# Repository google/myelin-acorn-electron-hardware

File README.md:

# MOVED to https://github.com/myelin/acorn-hardware

Any future development will happen over there.

myelin-acorn-electron-hardware
==============================

The [Acorn Electron](https://en.wikipedia.org/wiki/Acorn_Electron) is a British computer that was very popular in the UK and New
Zealand in the 80s, and was the first computer I ever used, in 1985.  I acquired
one on eBay in 2016, and started hacking on hardware expansions for it a little
later.  In the meantime I've also acquired a BBC Model B, and some BBC Master
128 motherboards.  This repository contains various hardware expansions I've
designed for the three machines.

Background: https://www.theregister.co.uk/2013/08/23/acorn_electron_history_at_30/

Designed by Phillip Pearson (philpearson@google.com)

This is not an official Google product.

Acorn Electron projects
-----------------------

- [standalone_cartridge_programmer](standalone_cartridge_programmer/):
  USB Acorn Electron cartridge interface, allowing read/write access
  to cartridges without an actual Electron / Plus 1.  (Built,
  verified.)

- [elk_pi_tube_direct](elk_pi_tube_direct/): Acorn Electron cartridge
  using a CPLD to provide address decoding and level shifting for a
  Raspberry Pi running PiTubeDirect.  (Built, verified.)

- [expansion_minispartan_breakout](expansion_minispartan_breakout/):
  Breakout board for the Electron's rear expansion connector, with
  buffers and footprint to attach a Scarab miniSpartan6+ LX25 board.
  (Built, verified.)

- [minus_one](minus_one/): Acorn Electron expansion that provides
  three Plus 1 workalike cartridge slots.  (Built, verified.)

- [32kb_flash_cartridge](32kb_flash_cartridge/): Simple Acorn Electron
  cartridge with two 16kB flash banks.  (Built, verified standard PCB.
  Mini PCB built but had a PCB error.)

Cross-platform projects
-----------------------

- [cpu_socket_expansion](cpu_socket_expansion/): Mezzanine board that attaches
  to the CPU socket of a BBC or Electron and translates between 5V TTL and 3.3V
  CMOS levels. (Built, tested.)

- [cpu_socket_minispartan_daughterboard](cpu_socket_minispartan_daughterboard/):
  Attaches to a cpu_socket_expansion board and connects a miniSpartan6+ FPGA
  board and a Raspberry Pi Zero running PiTubeDirect.  (Built, tested.)

- [spi_sd_card](spi_sd_card/): Experimental implementation of the interface
  used by MMFS to access SD cards, for the CPLD on an elk_pi_tube_direct board.
  (Code only.)

- [fx2_tube_cartridge_adapter](fx2_tube_cartridge_adapter/): Adapter to allow
  connecting an FX2-based logic analyzer board to the BBC Tube interface or
  as an Electron cartridge.  (Partly tested.)

- [bbc_power_distribution](bbc_power_distribution/): Small board to
  make it easy to power a Model B or Master motherboard from a 5V
  power supply with a barrel jack or Micro USB output.  Uses an
  LTC1983 to generate -5V, so you don't need to provide it externally.

BBC Model B projects
--------------------

- [new_bbc_bringup](new_bbc_bringup/): Notes on modernizing a BBC Model B,
  with flash and sideways RAM, and an emulated disk interface.

- [upurs_usb_port](upurs_usb_port/): Code to run on an ATMEGA32U4 to
  use it as a USB to serial adapter for UPURS.  (Flaky.)

- [serial_sd_adapter](serial_sd_adapter/): VHDL that runs on an
  elk_pi_tube_direct board and provides a fast serial port and SD card
  interface.  Also, a board that attaches to a BBC using the 1MHz Bus and
  provides the same interfaces.  (Built, tested serial port.  SD card interface
  untested.)

- [econet_from_scratch](econet_from_scratch/): USB Econet interface.
  (Untested.)

- [econet_hub](econet_hub/): Clock and bias circuit, with five Econet sockets,
  to connect a simple network together.  (Untested.)

BBC Master 128 projects
-----------------------

- [master_updateable_megarom](master_updateable_megarom/): BBC Master 128 MOS
  ROM replacement that can be reprogrammed while in the machine.  (Untested.)

- [emulated_keyboard](emulated_keyboard/): Code and VHDL to allow an attached
  computer to act as a keyboard for a BBC Master 128.  (Code only, verified.)

- [new_master_bringup](new_master_bringup/): Notes on getting a BBC Master 128
  motherboard to run without a keyboard or standard power supply.

Miscellaneous things that happened along the way
------------------------------------------------

- [atsamd11_pro_micro](atsamd11_pro_micro/): Tester board to experiment with
  USB on the Atmel ATSAMD11C14 chip.  (Untested.)

- [atsamd21_usb_host](atsamd21_usb_host/): Tester board to experiment with
  USB hosting on the Atmel ATSAMD21E18A chip.  (Untested.)

- [cherry_mx_keyswitch_tester](cherry_mx_keyswitch_tester/): Tester board to
  verify my Cherry MX keyswitch footprint before I order anything expensive.
  (Built, verified.)

Future project ideas
--------------------

- dual_ported_ram: Acorn Electron cartridge using a CPLD and a 128kB
  SRAM chip to implement dual ported RAM that can be read or written
  by both the Electron and a USB-attached computer.  (Working on the
  PCB layout.)

- expansion_debugger: Pro Micro, CPLD, and edge connector that can be
  connected to a Plus 1 or other Electron expansion for testing.
  (Just an idea so far.)

Installation notes
------------------

I use my own Python scripts for generating netlists, rather than entering
schematics through Kicad's eeschema package.  If you change the .py file in
any of the `pcb` folders, running 'make' (or 'make net') should rebuild the
netlist.

The Makefile will also plot gerbers once a .kicad_pcb file has been created.
This requires some messing around on macOS -- you have to copy the system
Python executable into the pcbnew folder.

Generating the previews linked from the `README.md` files requires pcb-tools,
which you can install using `python setup.py install` in the `third_party/pcb-tools` folder (after running `git submodule update --init`).  On macOS, first
install its dependencies with `brew install cairo pango`.

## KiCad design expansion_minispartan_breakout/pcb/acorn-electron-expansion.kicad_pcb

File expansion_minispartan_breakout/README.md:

expansion_minispartan_breakout
==============================

_Superseded by [cpu_socket_expansion](../cpu_socket_expansion/) and
[cpu_socket_minispartan_daughterboard](../cpu_socket_minispartan_daughterboard/)._

This board breaks out the expansion connector to 0.1" holes, and
provides the necessary level conversion and buffering to allow a
Scarab miniSpartan6+ board to interface with the Electron's expansion
connector.

I've assembled and tested one rev 1 board, with the miniSpartan6+ configured to
provide a few ROM banks, and it works pretty nicely.  I made some changes for
rev 2 to allow switching the direction of the address buffers, which would make
it possible to use a soft CPU in the FPGA (after removing the CPU from the
Electron's motherboard).  I never made a rev 2 board, however, as at that point
I [acquired a BBC Micro](../new_bbc_bringup/) and started working on more
portable hardware.

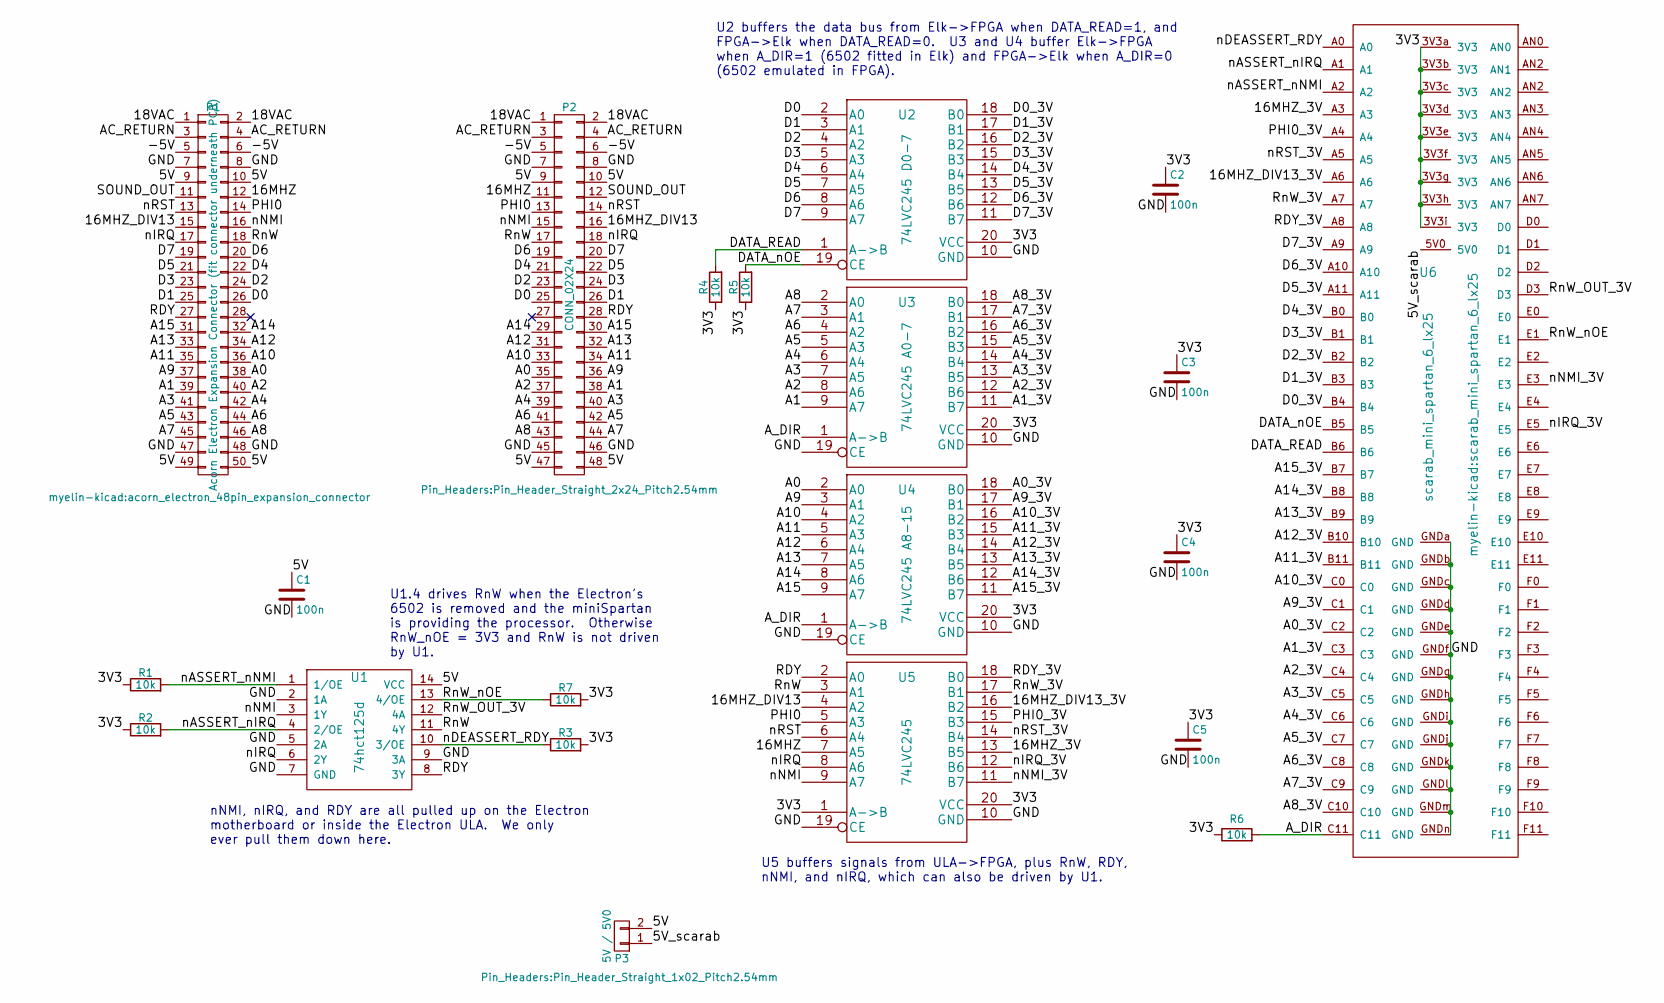
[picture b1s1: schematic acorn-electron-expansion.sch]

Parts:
C1, C2, C3, C4, C5: 100n; C0805_nosilkscreen
P1: Acorn Electron Expansion Connector (fit connector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; acorn_electron_48pin_expansion_connector
P2: CONN_02X24; Pin_Header_Straight_2x24_Pitch2.54mm
P3: 5V / 5V0; Pin_Header_Straight_1x02_Pitch2.54mm
R1, R2, R3, R4, R5: 10k; R0805_nosilkscreen
R6, R7: 10k; R_0805_HandSoldering
U1: 74hct125d; SOIC-14_3.9x8.7mm_Pitch1.27mm
U2: 74LVC245 D0-7; SSOP-20_4.4x6.5mm_Pitch0.65mm
U3: 74LVC245 A0-7; SSOP-20_4.4x6.5mm_Pitch0.65mm
U4: 74LVC245 A8-15; SSOP-20_4.4x6.5mm_Pitch0.65mm
U5: 74LVC245; SSOP-20_4.4x6.5mm_Pitch0.65mm
U6: scarab_mini_spartan_6_lx25

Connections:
/3V3: C2.1, C3.1, C4.1, C5.1, R1.1, R2.1, R3.2, R4.1, R5.1, R6.1, R7.2, U2.20 (VCC), U3.20 (VCC), U4.20 (VCC), U5.1 (A->B), U5.20 (VCC), U6.3V3a (3V3), U6.3V3b (3V3), U6.3V3c (3V3), U6.3V3d (3V3), U6.3V3e (3V3), U6.3V3f (3V3), U6.3V3g (3V3), U6.3V3h (3V3), U6.3V3i (3V3)
/5V: C1.1, P1.9, P1.10, P1.49, P1.50, P2.9, P2.10, P2.47, P2.48, P3.2, U1.14 (VCC)
/5V_scarab: P3.1, U6.5V0
/16MHZ: P1.12, P2.11, U5.7 (A5)
/16MHZ_3V: U5.13 (B5), U6.A3
/16MHZ_DIV13: P1.15, P2.16, U5.4 (A2)
/16MHZ_DIV13_3V: U5.16 (B2), U6.A6
/18VAC: P1.1, P1.2, P2.1, P2.2
/-5V: P1.5, P1.6, P2.5, P2.6
/A0: P1.38, P2.35, U4.2 (A0)
/A0_3V: U4.18 (B0), U6.C2
/A1: P1.39, P2.38, U3.9 (A7)
/A1_3V: U3.11 (B7), U6.C3
/A2: P1.40, P2.37, U3.8 (A6)
/A2_3V: U3.12 (B6), U6.C4
/A3: P1.41, P2.40, U3.7 (A5)
/A3_3V: U3.13 (B5), U6.C5
/A4: P1.42, P2.39, U3.6 (A4)
/A4_3V: U3.14 (B4), U6.C6
/A5: P1.43, P2.42, U3.5 (A3)
/A5_3V: U3.15 (B3), U6.C7
/A6: P1.44, P2.41, U3.4 (A2)
/A6_3V: U3.16 (B2), U6.C8
/A7: P1.45, P2.44, U3.3 (A1)
/A7_3V: U3.17 (B1), U6.C9
/A8: P1.46, P2.43, U3.2 (A0)
/A8_3V: U3.18 (B0), U6.C10
/A9: P1.37, P2.36, U4.3 (A1)
/A9_3V: U4.17 (B1), U6.C1
/A10: P1.36, P2.33, U4.4 (A2)
/A10_3V: U4.16 (B2), U6.C0
/A11: P1.35, P2.34, U4.5 (A3)
/A11_3V: U4.15 (B3), U6.B11
/A12: P1.34, P2.31, U4.6 (A4)
/A12_3V: U4.14 (B4), U6.B10
/A13: P1.33, P2.32, U4.7 (A5)
/A13_3V: U4.13 (B5), U6.B9
/A14: P1.32, P2.29, U4.8 (A6)
/A14_3V: U4.12 (B6), U6.B8
/A15: P1.31, P2.30, U4.9 (A7)
/A15_3V: U4.11 (B7), U6.B7
/AC_RETURN: P1.3, P1.4, P2.3, P2.4
/A_DIR: R6.2, U3.1 (A->B), U4.1 (A->B), U6.C11
/D0: P1.26, P2.25, U2.2 (A0)
/D0_3V: U2.18 (B0), U6.B4
/D1: P1.25, P2.26, U2.3 (A1)
/D1_3V: U2.17 (B1), U6.B3
/D2: P1.24, P2.23, U2.4 (A2)
/D2_3V: U2.16 (B2), U6.B2
/D3: P1.23, P2.24, U2.5 (A3)
/D3_3V: U2.15 (B3), U6.B1
/D4: P1.22, P2.21, U2.6 (A4)
/D4_3V: U2.14 (B4), U6.B0
/D5: P1.21, P2.22, U2.7 (A5)
/D5_3V: U2.13 (B5), U6.A11
/D6: P1.20, P2.19, U2.8 (A6)
/D6_3V: U2.12 (B6), U6.A10
/D7: P1.19, P2.20, U2.9 (A7)
/D7_3V: U2.11 (B7), U6.A9
/DATA_READ: R4.2, U2.1 (A->B), U6.B6
/DATA_nOE: R5.2, U2.19 (CE), U6.B5
/GND: C1.2, C2.2, C3.2, C4.2, C5.2, P1.7, P1.8, P1.47, P1.48, P2.7, P2.8, P2.45, P2.46, U1.2 (1A), U1.5 (2A), U1.7 (GND), U1.9 (3A), U2.10 (GND), U3.10 (GND), U3.19 (CE), U4.10 (GND), U4.19 (CE), U5.10 (GND), U5.19 (CE), U6.GNDa (GND), U6.GNDb (GND), U6.GNDc (GND), U6.GNDd (GND), U6.GNDe (GND), U6.GNDf (GND), U6.GNDg (GND), U6.GNDh (GND), U6.GNDi (GND), U6.GNDj (GND), U6.GNDk (GND), U6.GNDl (GND), U6.GNDm (GND), U6.GNDn (GND)
/PHI0: P1.14, P2.13, U5.5 (A3)
/PHI0_3V: U5.15 (B3), U6.A4
/RDY: P1.27, P2.28, U1.8 (3Y), U5.2 (A0)
/RDY_3V: U5.18 (B0), U6.A8
/RnW: P1.18, P2.17, U1.11 (4Y), U5.3 (A1)
/RnW_3V: U5.17 (B1), U6.A7
/RnW_OUT_3V: U1.12 (4A), U6.D3
/RnW_nOE: R7.1, U1.13 (4/OE), U6.E1
/SOUND_OUT: P1.11, P2.12
/nASSERT_nIRQ: R2.2, U1.4 (2/OE), U6.A1
/nASSERT_nNMI: R1.2, U1.1 (1/OE), U6.A2
/nDEASSERT_RDY: R3.1, U1.10 (3/OE), U6.A0
/nIRQ: P1.17, P2.18, U1.6 (2Y), U5.8 (A6)
/nIRQ_3V: U5.12 (B6), U6.E5
/nNMI: P1.16, P2.15, U1.3 (1Y), U5.9 (A7)
/nNMI_3V: U5.11 (B7), U6.E3
/nRST: P1.13, P2.14, U5.6 (A4)
/nRST_3V: U5.14 (B4), U6.A5

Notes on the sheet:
U1.4 drives RnW when the Electron's 6502 is removed and the miniSpartan is providing the processor. Otherwise RnW_nOE = 3V3 and RnW is not driven by U1.
nNMI, nIRQ, and RDY are all pulled up on the Electron motherboard or inside the Electron ULA. We only ever pull them down here.
U2 buffers the data bus from Elk->FPGA when DATA_READ=1, and FPGA->Elk when DATA_READ=0. U3 and U4 buffer Elk->FPGA when A_DIR=1 (6502 fitted in Elk) and FPGA->Elk when A_DIR=0 (6502 emulated in FPGA).
U5 buffers signals from ULA->FPGA, plus RnW, RDY, nNMI, and nIRQ, which can also be driven by U1.

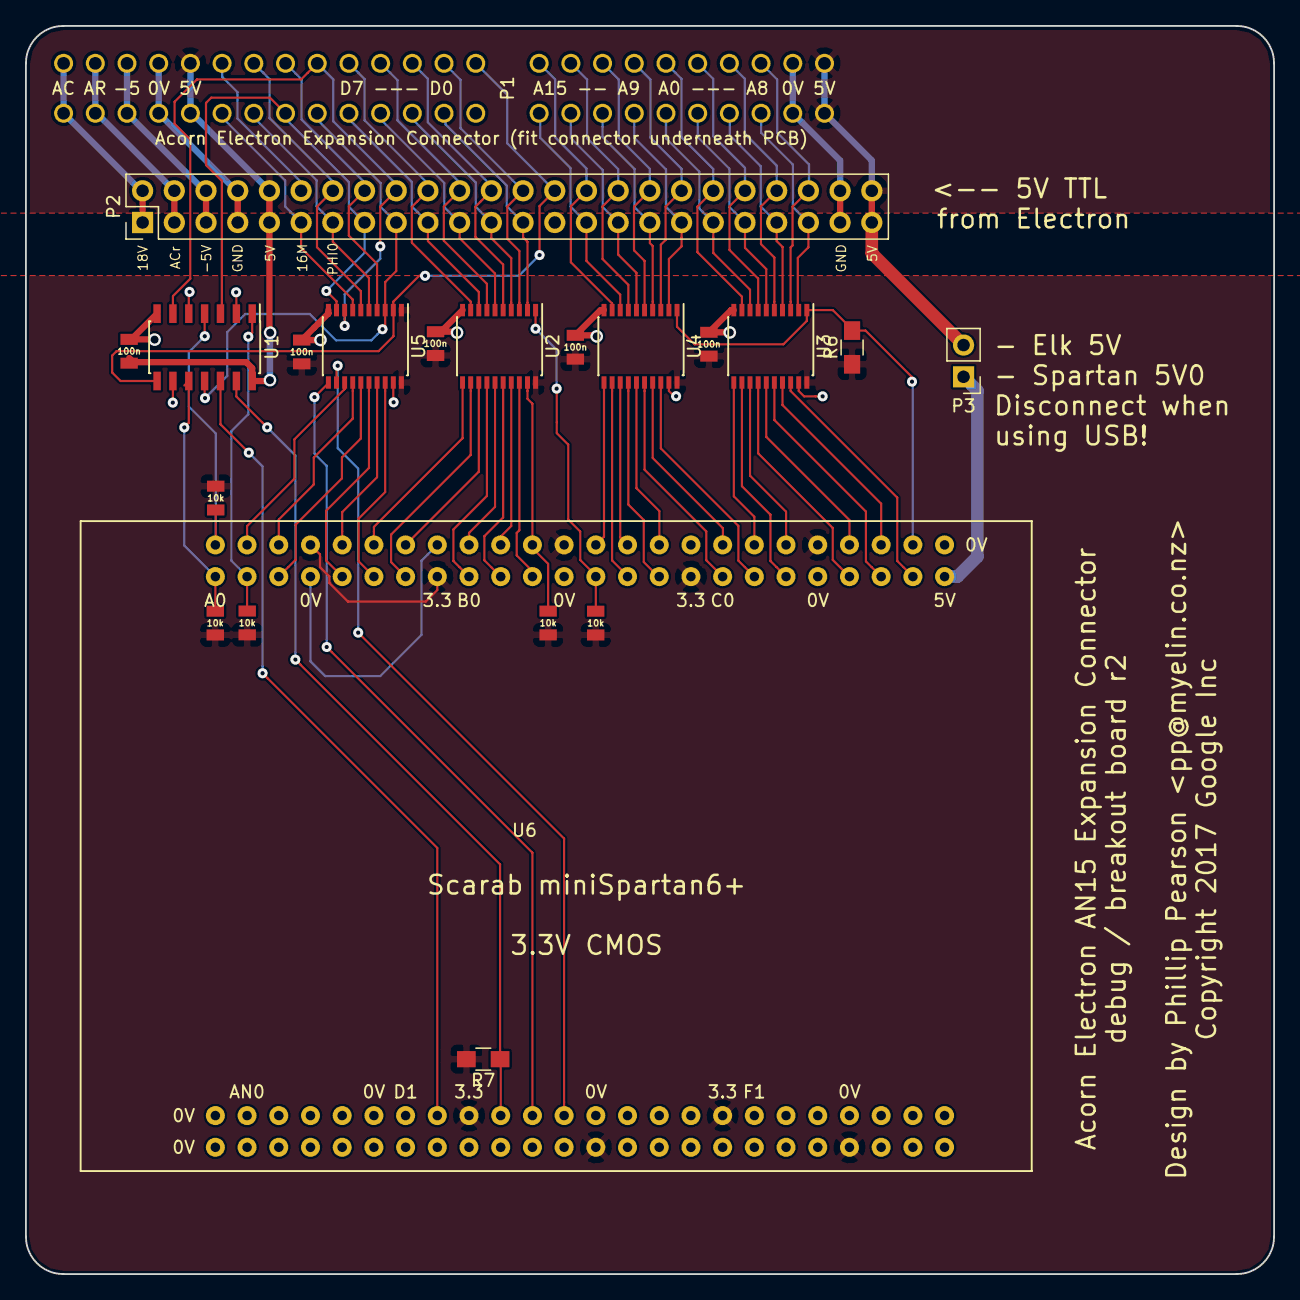
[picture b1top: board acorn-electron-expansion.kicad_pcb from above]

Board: 2 copper layers, 100.0 x 100.0 mm, 21 parts (0 on the bottom side), 80 nets.

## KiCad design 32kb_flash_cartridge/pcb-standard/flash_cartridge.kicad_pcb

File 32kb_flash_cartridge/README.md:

32kb_flash_cartridge
====================

This is a simple Acorn Electron cartridge that provides two 16kB flash
banks using a cheap 128kB SST39SF010A flash chip and a 74HCT00 quad
NAND gate.

I've made various different PCBs for this:

- original version (unreleased): this was based on [Paul Boddie's
  Electron breakout
  cartridge](http://hgweb.boddie.org.uk/AcornElectronCartridge).  This
  was my first PCB design for the Electron, and aside from one logic
  error (fixed by drilling out a track and adding a jumper wire) it
  works perfectly.

- [pcb-standard](pcb-standard/): This is designed to match the form
  factor of the PCBs used by Acornsoft for its ROM software.  I've
  built and tested one of these, and it works perfectly with no
  modifications.

- [pcb-mini](pcb-mini/): This is designed to just barely protrude from
  the Plus 1 when plugged in.  Unfortunately I forgot to re-pour the
  power and ground planes before generating gerbers to send off to the
  fab, and several data lines are shorted to ground in the units that
  I have.

[Discussion on the Stardot forums](http://stardot.org.uk/forums/viewtopic.php?f=3&t=12730).

Standard PCB:

Mini PCB:

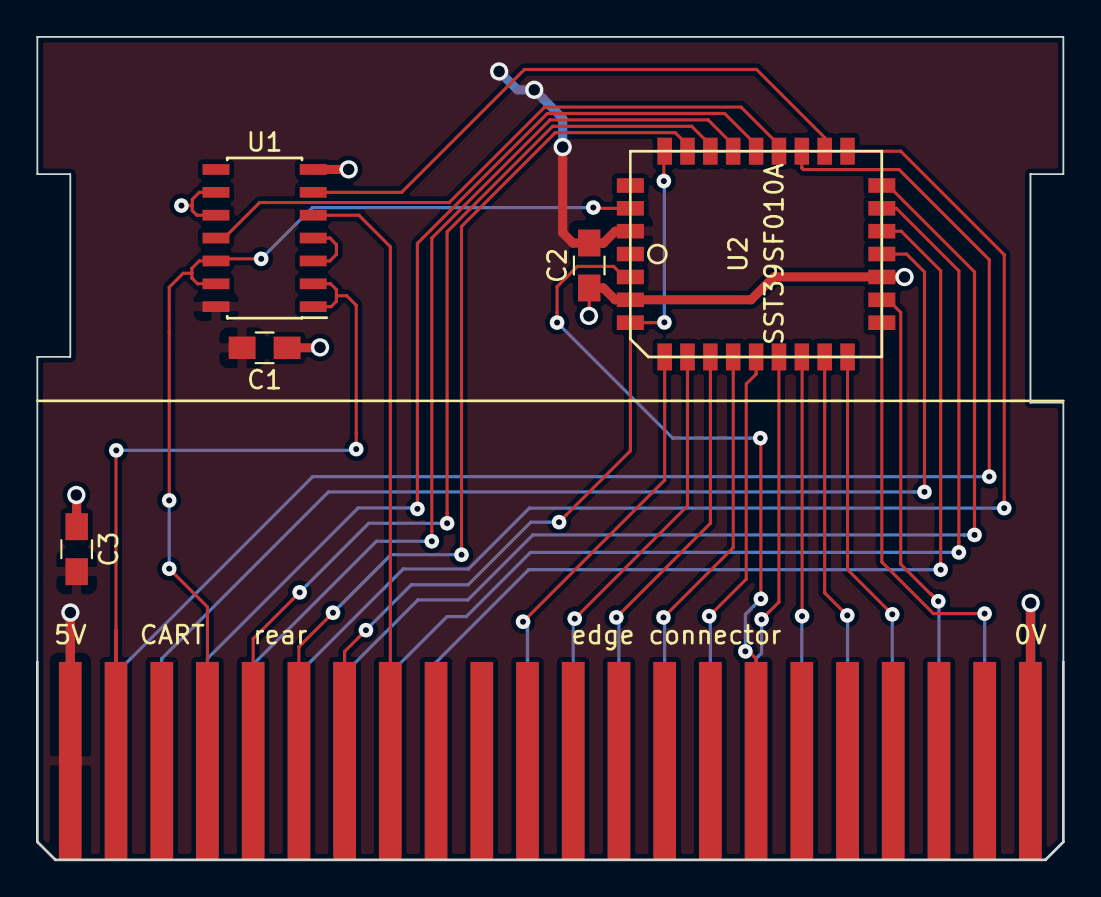
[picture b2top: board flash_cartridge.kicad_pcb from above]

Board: 2 copper layers, 57.0 x 45.7 mm, 6 parts (0 on the bottom side), 31 nets.

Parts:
C1, C2: 100n; C_0805_HandSoldering
C3: 10u; C_0805_HandSoldering
CART: edge connector; acorn_electron_cartridge_edge_connector
U1: 74HCT00; SOIC-14_3.9x8.7mm_Pitch1.27mm
U2: SST39SF010A; sst_plcc32_nh

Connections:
5V: C1.1, C2.1, C3.1, CART.A1, CART.B1, U1.14, U2.32
GND: C1.2, C2.2, C3.2, CART.A22, CART.B22, U1.7, U1.9, U1.10, U2.3, U2.16
elk_A0: CART.B18, U2.12
elk_A1: CART.B17, U2.11
elk_A2: CART.B16, U2.10
elk_A3: CART.B15, U2.9
elk_A4: CART.B14, U2.8
elk_A5: CART.B13, U2.7
elk_A6: CART.B12, U2.6
elk_A7: CART.B11, U2.5
elk_A8: CART.A5, U2.27
elk_A9: CART.B5, U2.26
elk_A10: CART.B2, U2.23
elk_A11: CART.B4, U2.25
elk_A12: CART.A7, U2.4, U2.29
elk_A13: CART.A6, U2.28
elk_D0: CART.B19, U2.13
elk_D1: CART.B21, U2.14
elk_D2: CART.B20, U2.15
elk_D3: CART.B3, U2.17
elk_D4: CART.B9, U2.18
elk_D5: CART.B8, U2.19
elk_D6: CART.B7, U2.20
elk_D7: CART.B6, U2.21
elk_PHI0: CART.A8, U1.5
elk_ROMQA: CART.A16, U2.2
elk_RnW: CART.A4, U1.12, U1.13, U2.31
elk_nOE: CART.A2, U1.1, U1.2
flash_nCE: U1.6, U2.22
flash_nOE: U1.11, U2.24
not_elk_nOE: U1.3, U1.4

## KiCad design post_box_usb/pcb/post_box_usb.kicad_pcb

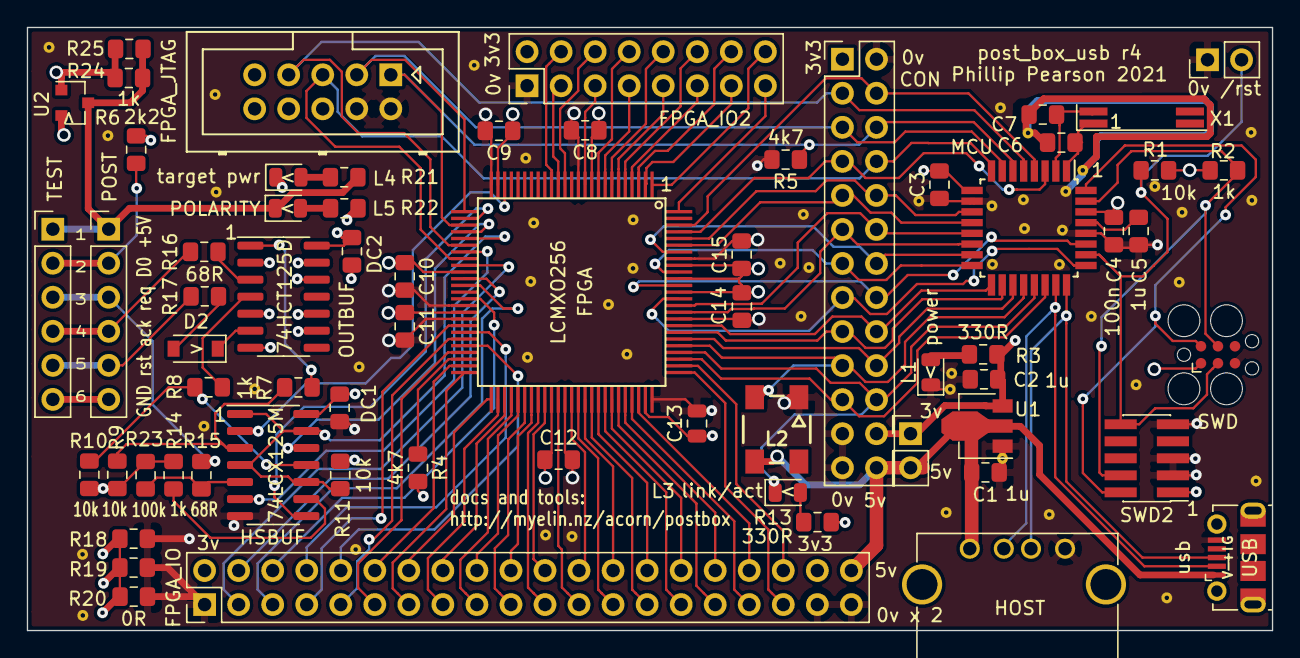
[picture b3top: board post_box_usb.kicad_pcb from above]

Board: 4 copper layers, 92.9 x 45.0 mm, 116 parts (0 on the bottom side), 105 nets.

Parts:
C1, C2, C5: 1u; C_0805_2012Metric_Pad1.15x1.40mm_HandSolder
C3, C4, C8, C9, C10, C11, C12, C14, C15: 100n; C_0805_2012Metric_Pad1.15x1.40mm_HandSolder
C6, C7: NF 15p; C_0805_2012Metric_Pad1.15x1.40mm_HandSolder
C13: 100n; C_0805_2012Metric
CON: NF pins; PinHeader_2x13_P2.54mm_Vertical
D2: BAT54; D_SOD-123
DC1, DC2: 100n; C_0805_2012Metric_Pad1.15x1.40mm_HandSolder
FPGA: LCMXO256; lattice_tn100
FPGA_IO: NF pins; PinHeader_2x20_P2.54mm_Vertical
FPGA_IO2: NF pins; PinHeader_2x08_P2.54mm_Vertical
FPGA_JTAG: NF lattice jtag; Multicomp_MC9A12-1034_2x05_P2.54mm_Vertical
HOST: NF usb host; USB_A
HSBUF: 74LCX125M; SOIC-14_3.9x8.7mm_P1.27mm
L1: power; LED_0805_2012Metric
L2: WS2812B-V5; WS2812B_PP
L3: link/act; LED_0805_2012Metric
L4: target pwr; LED_0805_2012Metric
L5: POLARITY; LED_0805_2012Metric
MCU: ATSAMD21E18A-AU; TQFP-32_7x7mm_Pitch0.8mm
OUTBUF: 74HCT125D; SOIC-14_3.9x8.7mm_P1.27mm
POST: pins; PinHeader_1x06_P2.54mm_Vertical
PWR: NF power; Pin_Header_Straight_1x02_Pitch2.54mm
R1, R9, R10, R11: 10k; R_0805_2012Metric_Pad1.15x1.40mm_HandSolder
R2, R7, R8, R14, R24, R25: 1k; R_0805_2012Metric_Pad1.15x1.40mm_HandSolder
R3, R13, R21, R22: 330R; R_0805_2012Metric_Pad1.15x1.40mm_HandSolder
R4, R5: 4k7; R_0805_2012Metric_Pad1.15x1.40mm_HandSolder
R6: 2k2; R_0805_2012Metric_Pad1.15x1.40mm_HandSolder
R15, R16, R17: 68R; R_0805_2012Metric_Pad1.15x1.40mm_HandSolder
R18, R19: NF 0R; R_0805_2012Metric_Pad1.15x1.40mm_HandSolder
R20: 0R; R_0805_2012Metric_Pad1.15x1.40mm_HandSolder
R23: 100k; R_0805_2012Metric_Pad1.15x1.40mm_HandSolder
RST: NF reset; Pin_Header_Straight_1x02_Pitch2.54mm
SWD: swd; Tag-Connect_TC2030-IDC-FP_2x03_P1.27mm_Vertical
SWD2: swd; PinHeader_2x05_P1.27mm_Vertical_SMD
TEST: NF pins; PinHeader_1x06_P2.54mm_Vertical
U1: MCP1700T-3302E/MB; SOT-89-3
U2: PMV65XP,215; SOT-23
USB: usb; USB_Micro-B_Molex-105017-0001
X1: NF MC146 32768Hz; Crystal_SMD_SeikoEpson_MC146-4pin_6.7x1.5mm_HandSoldering
staple_single1, staple_single2, staple_single3, staple_single4, staple_single5, staple_single6, staple_single7, staple_single8, staple_single9, staple_single10, staple_single11, staple_single12, staple_single13, staple_single14, staple_single15, staple_single16, staple_single17, staple_single18, staple_single19, staple_single20, staple_single21, staple_single22, staple_single23, staple_single24, staple_single25, staple_single26, staple_single27, staple_single28, staple_single29, staple_single30, staple_single31, staple_single32, staple_single33, staple_single34, staple_single35, staple_single36, staple_single37, staple_single38, staple_single39, staple_single40, staple_single41, staple_single42, staple_single43, staple_single44, staple_single45, staple_single46, staple_single47, staple_single48, staple_single49, staple_single50: via_single

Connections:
3V3: C2.1, C3.2, C4.2, C8.1, C9.1, C10.1, C11.1, C12.1, C13.1, C14.1, C15.1, CON.1, CON.24, DC1.2, FPGA.10, FPGA.24, FPGA.35, FPGA.41, FPGA.60, FPGA.74, FPGA.88, FPGA.90, FPGA.92, FPGA_IO.2, FPGA_IO.38, FPGA_IO2.2, FPGA_JTAG.6, HSBUF.14, MCU.9, MCU.30, PWR.1, R1.2, R2.2, R3.1, R4.2, R11.2, R13.1, SWD.1, SWD2.1, U1.3
5V: C1.2, CON.26, FPGA_IO.40, HOST.1, L2.1, PWR.2, U1.2, USB.1
GND: C1.1, C2.2, C3.1, C4.1, C5.1, C6.1, C7.1, C8.2, C9.2, C10.2, C11.2, C12.2, C13.2, C14.2, C15.2, CON.2, CON.23, CON.25, DC1.1, FPGA.12, FPGA.25, FPGA.40, FPGA.42, FPGA.62, FPGA.75, FPGA.84, FPGA.93, FPGA_IO.1, FPGA_IO.37, FPGA_IO.39, FPGA_IO2.1, FPGA_JTAG.2, FPGA_JTAG.4, HOST.4, HSBUF.7, L1.1, L2.3, MCU.10, MCU.28, R5.2, R18.2, R19.2, R20.2, RST.1, SWD.5, SWD2.3, SWD2.5, SWD2.9, U1.1, USB.5, staple_single1.1, staple_single2.1, staple_single3.1, staple_single4.1, staple_single5.1, staple_single6.1, staple_single7.1, staple_single8.1, staple_single9.1, staple_single10.1, staple_single11.1, staple_single12.1, staple_single13.1, staple_single14.1, staple_single15.1, staple_single16.1, staple_single17.1, staple_single18.1, staple_single19.1, staple_single20.1, staple_single21.1, staple_single22.1, staple_single23.1, staple_single24.1, staple_single25.1, staple_single26.1, staple_single27.1, staple_single28.1, staple_single29.1, staple_single30.1, staple_single31.1, staple_single32.1, staple_single33.1, staple_single34.1, staple_single35.1, staple_single36.1, staple_single37.1, staple_single38.1, staple_single39.1, staple_single40.1, staple_single41.1, staple_single42.1, staple_single43.1, staple_single44.1, staple_single45.1, staple_single46.1, staple_single47.1, staple_single48.1, staple_single49.1, staple_single50.1
PA02: CON.7, FPGA.97, MCU.3
PA03: CON.4, FPGA.98, MCU.4
PA16: CON.18, FPGA.83, MCU.17
PA17: CON.17, FPGA.82, MCU.18
PA18: CON.20, FPGA.81, MCU.19
PA19: CON.19, FPGA.80, L2.4, MCU.20
PA27: CON.15, FPGA.87, MCU.25
SLEEPN: FPGA.48, R4.1
USBDM: HOST.2, MCU.23, USB.2
USBDP: HOST.3, MCU.24, USB.3
VDDCORE: C5.2, MCU.29
XTAL_IN: C6.2, MCU.1, X1.1
XTAL_OUT: C7.2, MCU.2, X1.4
fpga_GPIO0: FPGA.34, FPGA_IO.3
fpga_GPIO1: FPGA.36, FPGA_IO.4
fpga_GPIO2: FPGA.37, FPGA_IO.5
fpga_GPIO3: FPGA.39, FPGA_IO.6
fpga_GPIO4: FPGA.43, FPGA_IO.7
fpga_GPIO5: FPGA.44, FPGA_IO.8
fpga_GPIO6: FPGA.45, FPGA_IO.9
fpga_GPIO7: FPGA.46, FPGA_IO.10
fpga_GPIO8: FPGA.47, FPGA_IO.11
fpga_GPIO9: FPGA.49, FPGA_IO.12
fpga_GPIO10: FPGA.50, FPGA_IO.13
fpga_GPIO11: FPGA.51, FPGA_IO.14
fpga_GPIO12: FPGA.52, FPGA_IO.15
fpga_GPIO13: FPGA.53, FPGA_IO.16
fpga_GPIO14: FPGA.54, FPGA_IO.17
fpga_GPIO15: FPGA.55, FPGA_IO.18
fpga_GPIO16: FPGA.56, FPGA_IO.19
fpga_GPIO17: FPGA.57, FPGA_IO.20
fpga_GPIO18: FPGA.58, FPGA_IO.21
fpga_GPIO19: FPGA.59, FPGA_IO.22
fpga_GPIO20: FPGA.61, FPGA_IO.23
fpga_GPIO21: FPGA.63, FPGA_IO.24
fpga_GPIO22: FPGA.64, FPGA_IO.25
fpga_GPIO23: FPGA.65, FPGA_IO.26
fpga_GPIO24: FPGA.66, FPGA_IO.27
fpga_GPIO25: FPGA.67, FPGA_IO.28
fpga_GPIO26: FPGA.68, FPGA_IO.29
fpga_GPIO27: FPGA.69, FPGA_IO.30
fpga_GPIO28: FPGA.70, FPGA_IO.31
fpga_GPIO29: FPGA.71, FPGA_IO.32
fpga_GPIO30: FPGA.72, FPGA_IO.33
fpga_GPIO31: FPGA.73, FPGA_IO.34
fpga_GPIO32: FPGA.76, FPGA_IO.35
fpga_GPIO33: FPGA.77, FPGA_IO.36
fpga_GPIO34: FPGA.15, FPGA_IO2.3
fpga_GPIO35: FPGA.16, FPGA_IO2.4
fpga_GPIO36: FPGA.11, FPGA_IO2.5
fpga_GPIO37: FPGA.14, FPGA_IO2.6
fpga_GPIO38: FPGA.8, FPGA_IO2.7
fpga_GPIO39: FPGA.9, FPGA_IO2.8
fpga_GPIO40: FPGA.6, FPGA_IO2.9
fpga_GPIO41: FPGA.7, FPGA_IO2.10
fpga_GPIO42: FPGA.4, FPGA_IO2.11
fpga_GPIO43: FPGA.5, FPGA_IO2.12
fpga_GPIO44: FPGA.2, FPGA_IO2.13
fpga_GPIO45: FPGA.3, FPGA_IO2.14
fpga_GPIO46: FPGA.100, FPGA_IO2.15
fpga_GPIO47: FPGA.1, FPGA_IO2.16
fpga_TCK: CON.6, FPGA.28, FPGA_JTAG.1, MCU.6, R5.1
fpga_TDI: CON.8, FPGA.33, FPGA_JTAG.5, MCU.8
fpga_TDO: CON.3, FPGA.31, FPGA_JTAG.7, MCU.5
fpga_TMS: CON.5, FPGA.26, FPGA_JTAG.3, MCU.7
fpga_clock_48mhz: CON.12, FPGA.86, MCU.13
fpga_spi_cs: CON.14, FPGA.94, MCU.15
fpga_spi_miso: CON.13, FPGA.91, MCU.16
fpga_spi_mosi: CON.10, FPGA.96, MCU.11
fpga_spi_sck: CON.9, FPGA.95, MCU.12
hotswap_noe: FPGA.30, HSBUF.1, HSBUF.4, HSBUF.10, HSBUF.13, R11.1
mcu_RESET: MCU.26, R1.1, RST.2, SWD.3, SWD2.10
mcu_RXD: CON.21, FPGA.78, MCU.22
mcu_SWCLK: MCU.31, R2.1, SWD.4, SWD2.4
mcu_SWDIO: MCU.32, SWD.2, SWD2.2
mcu_TXD: CON.22, FPGA.79, L3.1, MCU.21
mcu_txd_led_anode: L3.2, R13.2
power_led_anode: L1.2, R3.2
reset_in: CON.16, FPGA.89, MCU.27
target_5V: DC2.2, OUTBUF.2, OUTBUF.10, OUTBUF.13, OUTBUF.14, R6.2, R9.2, R10.2, R14.1, R23.2, U2.2
target_5V_ext: L5.1, POST.1, R21.1, R24.1, R25.1, TEST.1, U2.3
target_5V_r: HSBUF.9, R14.2
target_D0: POST.2, R6.1, TEST.2
target_GND: DC2.1, L4.1, OUTBUF.5, OUTBUF.7, OUTBUF.9, OUTBUF.12, POST.6, R18.1, R19.1, R20.1, R22.1, R24.2, R25.2, TEST.6, U2.1
target_power_3v: FPGA.27, HSBUF.8
target_power_led_anode: L4.2, R21.2
target_power_out: CON.11, FPGA.85, MCU.14
target_power_reversed_led_anode: L5.2, R22.2
target_reset: D2.1, OUTBUF.6
target_reset_ext: POST.5, R17.1, TEST.5
target_reset_noe: FPGA.29, HSBUF.12
target_reset_noe_buf: HSBUF.11, R8.1, R10.1
target_reset_noe_buf_r: OUTBUF.4, R8.2
target_reset_prediode: D2.2, R17.2
target_testack: OUTBUF.3, R16.2
target_testack_ext: POST.4, R16.1, TEST.4
target_testreq: HSBUF.5, R15.2, R23.1
target_testreq_ext: POST.3, R15.1, TEST.3
testack_noe: FPGA.23, HSBUF.2
testack_noe_buf: HSBUF.3, R7.1, R9.1
testack_noe_buf_r: OUTBUF.1, R7.2
testreq_3v: FPGA.32, HSBUF.6

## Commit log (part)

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2017-10-31 Fixed up drill file building -- it doesn't appear to work until the plotter has been closed
2017-10-31 Cherry MX keyswitch footprint tester
2017-11-01 Generate .png renders of boards when making fab outputs
2017-11-01 elk_pi_tube_direct: Update to new rendering code and defaults, and add preview to README
2017-11-01 Added notes for all projects
2017-11-01 Update serial_sd_adapter to new system and add previews
2017-11-01 Update cpu_socket_expansion to new system and add previews
2017-11-01 Fixed link to new_master_bringup
2017-11-02 Forgot to add this: initial setup script
2017-11-02 Added missing project file
2017-11-02 Script to pack a file into a .uef, then generate a .wav file that can be loaded on an Electron/BBC
2017-11-02 minus_one: Default to ROM 13 so we don't accidentally drive the bus
2017-11-08 atsamd21_usb_host: Breakout board with an ATSAMD21 chip and a USB-A socket (and a micro USB socket)
2017-11-10 econet_from_scratch: Partial design for a USB Econet interface
2017-11-10 Added mention of econet_from_scratch
2017-11-12 'make' now just builds everything, rather than rebuilding everything
2017-11-14 Added more SERCOM info for atsamd11_pro_micro
2017-11-15 econet_hub: Socket box + clock + termination for a small Econet network
2017-11-17 uef-utils: forgot to check this in back when I started depending on it
2017-11-17 Ported Electron code over to work on the 1MHz Bus board
2017-11-19 Ignoring one annoying file that keeps popping up locally
2017-11-19 cpu_socket_minispartan_daughterboard: Copied expansion_minispartan_breakout/fpga-basic to start with
2017-11-19 Added econet_hub to top level README
2017-11-19 Added picture of a Pro Micro running upurs_usb_port firmware, connected to a User Port
2017-11-19 Added picture of prototype spi_sd_card
2017-11-20 Split out all ext_GP signals, tidied VHDL, shuffled signals to make the defaults safer
2017-11-21 MMFS and PiTubeDirect now work with cpu_socket_minispartan_daughterboard
2017-11-27 Updated netlist as per hoglet's recommendations in http://www.stardot.org.uk/forums/viewtopic.php?f=3&t=13882&p=186963#p186908
2017-11-29 Updated README with latest project status
2017-11-30 fx2_tube_cartridge_adapter: routed cartridge to tube connections
2017-12-06 fx2_tube_cartridge_adapter: Routed CPLD and most other signals
2017-12-07 rom_socket_level_shifter: DRC passes, board probably works, but looks extremely ugly
2017-12-07 bbc_power_distribution is ready to go
2017-12-07 econet_from_scratch is ready to go
2017-12-20 fx2_tube_cartridge_adapter: Works nicely on an Electron
2017-12-28 bga_in_two_layers: pinout stable; now to try to connect pins to chip
2018-01-01 Fixed elk_pi_tube_direct link
2018-01-03 Added bill of materials for fx2tube
2018-01-05 Update fx2_tube_cartridge_adapter docs to explain current status
2018-01-05 Added cartridge port detection based on presence of 16MHz clock
2018-01-09 Renamed current keyboard emulator prototype files to avoid confusion when I start on the next version
2018-01-14 Renumbered IO* pins to match connector pinout
2018-01-20 r2: Added a bunch of TODOs, implemented some, made silkscreen more assembly-friendly
2018-02-01 10m04_cpu_socket project, with working RAM in &FD00 (using &FCF0 as the paging register)
2018-02-21 master_updateable_megarom code/hdl dump -- partially working
2018-02-21 Set CPLD pins to slow slew rate
2018-02-21 Fixed it by changing cpld_SS to a synchronous reset. Ready for others to try now.
2018-02-24 Added script to patch rom images into a 128kB megarom image, and explained how to use it in the README
2018-03-05 Added TODO and notes on the state of the upurs_usb_port code
2018-04-27 Starting on a Verilog Econet interface -- so far it receives bytes from the MCU and writes them to Econet. Reception not tested.
2018-04-28 More things to test
2018-05-04 Switch to using program_cpld.py to program the CPLD (xc3sprog will never work as the JTAG pins aren't exposed)
2018-06-04 Added .jed and .svf files for fx2_tube_cartridge_adapter, and added a 'make local' option
2018-06-05 simple_cpld_programmer -- an untested way to program CPLDs using a Pro Micro
2018-06-05 Various updates to master_updateable_megarom: SCK reliability experiments, and mods to run in a Model B
2018-06-05 Added micro USB socket description to bbc_power_distribution
2018-06-05 Switched minus_one to new CPLD Makefile system and added .jed and .svf
2018-06-05 Sync latest econet_from_scratch/cpld changes, and update to new Makefile system
2018-06-05 Formatting consistency tweak
2018-06-05 Update build system for bbc_1mhz_bus_cpld but don't add .jed/.svf because this code is in flux
2018-06-05 Add timing constraints for avr_SCK and bbc_1MHZE
2018-06-05 Dual serial ports for bbc_1mhz_serial_cpld (without updating the .jed/.svf because this is unverified)
2018-06-06 Sync everything from 10m04_cpu_socket (from a few months back)
2018-08-05 Disable AVR SD pin override to make the SD card always work on boot Fixes #2
2018-10-04 econet_from_scratch: Figured out why nothing was working; the CPLD doesn't start a frame unless the first byte from the MCU has bit 8 set.
2018-10-21 libcrc by Lammert Bies
2018-10-24 libcrc: make update_crc_econet work like crc_econet
2018-11-23 In-progress A3000 ROM emulator board
2018-12-01 a3000_rom_emulator: all components placed, ready to route the big CPLD I think
2018-12-06 Added pics
2018-12-07 More tidying, plus added 30 ground staples, and removed some spurious lines from constraints.ucf
2018-12-11 Added some more staples
2018-12-17 Added pullup on A21, for predictable results when it's not wired to the motherboard
2018-12-17 support 4 layer boards and kicad 5
2018-12-18 Mainly silkscreen work, some tracking
2018-12-19 Updated RAM connector per cmorley's advice on Stardot: moved the left block of 20 pins 25 mils right
2018-12-21 arcflash ready for fab, I think
2018-12-22 Initial FPGA project for archimedes_bus_scope
2018-12-23 Added some FPGA config signals and got power vias looking good
2018-12-24 v1 board currently being fabbed at jlcpcb
2018-12-28 Regenerated component file including all parts (some were missing 'insert')
2018-12-29 Tidied all terminated signals so all signals are separated by the ground plane
2018-12-29 Updated renders to add staples
2019-01-03 Initial firmware, which can program the CPLD but not much else
2019-01-03 Successfully reading CFI block from both flash chips
2019-01-05 make python string raw
2019-01-05 Accelerated programming quite a bit by buffering 16kB of data
2019-01-07 A5000 adapter board for Arcflash project
2019-01-07 Wired up adapter, and brought out A21 for easy connection to arcflash board
2019-01-10 Attempting to create a new A3000 test ROM, built using modern tools
2019-01-11 Progress: the program now links, and appears to run OK in Arculator. One big glitch was that I didn't have .rodata in the text segment, and it was getting copied into .data, so my program was using t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
2019-01-13 A few script updates in preparation for merging https://github.com/google/myelin-acorn-electron-hardware/pull/4
2019-01-15 Harmonize tabs in UEFtrans.py -- there were a couple of locations where mixed tabs and spaces were being used for significant indentation, which will be a TabError in Python 3 (see https://github.com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
2019-01-19 Tracking Romcs* pulse and detecting when our signal words are being read
2019-01-20 Gave up on the serial_sd_adapter style comms and just hacked in a bit banged serial port. Just barely fits.
2019-01-27 Only refresh memory during video flyback, and turn off VIDC test mode on boot. Now the bootloader behaves the same in emulation and on real A3000 hardware.
2019-01-29 Update README and change tabs to spaces
2019-01-29 Successfully switching SERCOM2 between SPI and UART
2019-02-01 Bit banged serial port works for transmission; reception code is there but untested
2019-02-03 Untested code to read CMOS settings
2019-02-07 Moved a bunch of tracks to the bottom copper layer, to make room between them.
2019-02-07 Looking nice -- time for staples
2019-02-08 Realized I got the RPC ROMs backwards, so need to reroute or fix in software
2019-02-08 v1 ready to go to JLC
2019-02-11 Initializing keyboard and reading mouse
2019-02-12 Realized I can skip all the << 16 stuff by just making all IOC regs uint8_t*. More attempts to make keyboard init properly.
2019-02-14 Added support for 1M ROM banks. Changed memory map to allow 4 x 1M, 2 x 2M, 2 x 4M. Verified with 4MB RO320 image on my A3000.
2019-02-17 v2: 74lvt125 added and all lines routed, I think
2019-02-19 Adding stb_sprintf library
2019-02-19 nanopb from https://jpa.kapsi.fi/nanopb/download/nanopb-0.3.9.2.tar.gz, minus docs, tests, examples
2019-03-03 Another .ramfunc function; considering just moving everything into that section...
2019-03-04 python lib now generates proper flash images, and bootloader can now read protos
2019-03-06 New menu system seems to work
2019-03-06 Made kb/mouse debug info not mess up display
2019-03-16 Small board for a PCF8583 and supporting components, to help with fixing severely battery damaged Archimedes motherboards
2019-03-16 Arcflash RISC PC support -- the bootloader now includes a cut-down version of RISC OS, and boots on both Archimedes and RISC PC machines.
2019-04-28 remove conditional display of IOMD in banner, because IOMD bootloader doesn't use start.s at all
2019-04-28 Fix bug with padding -- it was only showing up when I had three 4MB images
2019-04-28 master_updateable_megarom changes from months ago; looks like a PCB rebuild and some minor CPLD tweaks
2019-04-28 Add supercap to pcf8583 daughterboard and make it a bit bigger, with mounting holes
2019-05-04 Python 3 compatibility, and now on PyPI
2019-05-05 Explain how to make a basic flash image
2019-06-04 Added some notes on how to build an SD card adapter for the Electron
2019-06-14 Tidied up Arcflash BOM and marked NF components
2019-06-24 econet hub v2
2019-06-24 template project for xc9500xl_44_breakout
2019-08-13 update Arduino-Makefile to latest upstream master
2019-09-08 Arcflash: comments about removing D2
2019-09-08 Arcflash v2 PCB change: use 74LVC125 instead of 74LVT125
2019-09-13 Successfully detecting RESET double-clicks, and resetting machine when OS selected in bootloader
2019-09-17 Arcflash bootloader successfully reads CMOS now
2019-11-10 MGC MKII: VHDL now builds; pins not assigned yet and substantial logic still missing. Uses 31/36 MCs -- may not be able to do fast SPI.
2019-11-15 MGC MKII: Moved SD_MISO input to bit 7 of FCD8, to match Plus 1 FC72
2019-11-17 MGC MKII: Re-enabled shift register; had to tie SD_CS2 high or fitting fails
2020-05-16 Allow remote server to be specified for Xilinx builds with REMOTE_HOST arg. Do remote Xilinx builds in a spcified parent dir rather than filling the remote home dir.
2020-05-27 The PCB is pretty ugly and many things still need to be connected up to the FPGA, but it just passed DRC for the first time, so I guess it's time for a commit.
2020-05-30 post_box_usb PCB r1 finished and sent to JLCPCB
2020-07-14 post_box_usb: r2 with an attempt at reverse polarity protection
2020-07-17 arcflash: v3 PCB with 68R resistor packs to provide some protection/damping to data lines
2020-07-25 arcflash: Make it possible to single or double sync Romcs*; doesn't appear to save any CPLD space though
2020-07-25 arcflash: Remove reset_arm and uncomment SPI logic gated by enable_comms
2020-12-11 post_box_usb: r3 candidate; resistors tweaked, diode replaced with mosfet, footprints fixed, test points added
2021-01-17 arcflash: Clarify that bottom-layer decoupling capacitors are optional
2021-01-20 arcflash: Add custom bootloader so we can use our own USB VID/PID
2021-01-20 arcflash: Add CPLD programming instructions
2021-01-20 arcflash: Add troubleshooting notes for firmware build, crash out on build errors, and use a better board-specific define
2021-01-23 simple_cpld_programmer: Port to Python 3; make firmware buildable using the Arduino IDE.
2021-01-25 arcflash: Update URLs to use new GitHub main branch
2021-01-26 Update common files and third_party submodules
2021-02-02 10m04_cpu_socket: export and reimport, to get rid of unused files
2021-03-06 arcflash: rename svf to path expected by 'make program'
2021-03-16 arcflash: Add flash continuity check command (K)
2021-07-19 post_box_usb: Start r4; generate JLCPCB BOM so I can get them to assemble these.
2025-01-14 arcflash: Notes on installing Xilinx ISE
2025-01-30 arcflash: Make os_switcher_bootloader buildable again
2025-04-30 Add ROM extractor Python script from 2020
2025-05-01 riscos_rom_tools: Add README

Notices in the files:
32kb_flash_cartridge/pcb-standard/flash_cartridge.kicad_pcb:
Copyright (C) 2017 Google Inc
a3000_rom_emulator/pcb/a3000_rom_emulator.kicad_pcb:
Copyright 2018 Google LLC
econet_hub/pcb/econet_hub.kicad_pcb:
Copyright 2017 Google LLC
expansion_minispartan_breakout/pcb/acorn-electron-expansion.kicad_pcb:
Copyright 2017 Google Inc
pcf8583_daughterboard/pcb/pcf8583_daughterboard.kicad_pcb:
Copyright 2019 Google LLC
post_box_usb/pcb/post_box_usb.kicad_pcb:
Copyright 2017-2021 Google Inc
